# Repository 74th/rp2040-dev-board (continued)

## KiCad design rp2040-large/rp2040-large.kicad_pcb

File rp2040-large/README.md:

# RP2040 large board

RP2040 を手ではんだづけするのにトライしてみた開発ボードです。

Raspberry Pi PICO と同じピンレイアウトで、Flash を好きなサイズのものに置き換えて使うことができます。

RP2040 の実装の際には、細く切ったマスキングテープを使って位置合わせをしてから、実装すると成功率が上がります。

## v1.5.2

- 回路図 [PDF](./rp2040-large-semantics-1.5.2.pdf) [kicanvas](https://kicanvas.org/?github=https%3A%2F%2Fgithub.com%2F74th%2Frp2040-dev-board%2Fblob%2Frp2040-large%2F1.5.2%2Frp2040-large%2Frp2040-large.kicad_sch)
- PCB [kicanvas](https://kicanvas.org/?github=https%3A%2F%2Fgithub.com%2F74th%2Frp2040-dev-board%2Fblob%2Frp2040-large%2F1.5.2%2Frp2040-large%2Frp2040-large.kicad_pcb)

### features

- USB 電源保護 IC として [CH213K](https://www.wch-ic.com/products/CH213.html) を追加

### BOM

| Reference           | Name                                  | Quantity |
| ------------------- | ------------------------------------- | -------- |
| C1, C4              | Capacitor 0805 10uF                   | 2        |
| C2, C3              | Capacitor 0805 10-33pF                | 2        |
| C5, C7, C10         | Capacitor 0805 1uF                    | 3        |
| C6, C8, C9, C11-C16 | Capacitor 0805 100nF                  | 9        |
| D1                  | LED 0805 RED                          | 1        |
| D2                  | LED 0805 BLUE                         | 1        |
| J1                  | USB Type-C Receptacle                 | 1        |
| R1, R11             | Resistor 0805 1kΩ                     | 2        |
| R2, R3, R7          | Resistor 0805 5.1kΩ                   | 3        |
| R4, R5              | Resistor 0805 27Ω                     | 2        |
| R6, R10             | Resistor 0805 10kΩ                    | 2        |
| R8                  | Resistor 0805 1RΩ                     | 1        |
| R9                  | Resistor 0805 200Ω                    | 1        |
| SW1, SW2            | Button SKRPABE010                     | 2        |
| U1                  | USB Power Protection IC SOT-23 CH213K | 1        |
| U2                  | Regulator 3.3V SOT-89 AMS1117-3.3     | 1        |
| U3                  | Flash SOIC-8 W25Q32JVS                | 1        |
| U4                  | MCU Raspberry Pi RP2040               | 1        |
| Y1                  | Crystal 3225 12MHz                    | 1        |

### BOM

## v1.4.0

- 回路図 [PDF](./rp2040-large-semantics-1.4.0.pdf) [kicanvas](https://kicanvas.org/?github=https%3A%2F%2Fgithub.com%2F74th%2Frp2040-dev-board%2Fblob%2Frp2040-large%2Fv1.4.0%2Frp2040-large%2Frp2040-large.kicad_sch)
- PCB [kicanvas](https://kicanvas.org/?github=https%3A%2F%2Fgithub.com%2F74th%2Frp2040-dev-board%2Fblob%2Frp2040-large%2Fv1.4.0%2Frp2040-large%2Frp2040-large.kicad_pcb)

| ID                         | package                             | Value   | Num |
| -------------------------- | ----------------------------------- | ------- | --- |
| C1,C2,C4,C6-C8,C10,C13,C16 | 0805in 2012mm SMD Capacitor         | 100nF   | 9   |
| C3,C5,C9                   | 0805in 2012mm SMD Capacitor         | 1uF     | 3   |
| C11,C12                    | 0603in 1608mm SMD Capacitor         | 27pF    | 2   |
| C14,C15                    | 0805in 2012mm SMD Capacitor         | 10uF    | 2   |
| R1,R2                      | 0805in 2012mm SMD Resistor          | 27.4R   | 2   |
| R3,R6                      | 0805in 2012mm SMD Resistor          | 1kR     | 2   |
| R7                         | 0805in 2012mm SMD Resistor          | 1kR(NC) | 1   |
| R4,R5                      | 0805in 2012mm SMD Resistor          | 5.1kR   | 2   |
| R8                         | 0805in 2012mm SMD Resistor          | 10kR    | 1   |
| R9                         | 0805in 2012mm SMD Resistor          | 200R    | 1   |
| R10                        | 0805in 2012mm SMD Resistor          | 1R      | 1   |
| U1                         | RP2040                              |         | 1   |
| U2                         | W25Q32BVSSIG                        |         | 1   |
| U3                         | AMS 1117-3.3V                       |         | 1   |
| P1                         | USB 2.0 Type-C MidMount Socket      |         | 1   |
| Y1                         | 3325mm SMD Quartz Resonator Crystal | 12MHz   | 1   |
| SW1,SW2                    | 3x4x2.5mm SMD Tactile Switch        |         | 2   |

## v1.3.1

| ID                         | package                             | Value | Num |
| -------------------------- | ----------------------------------- | ----- | --- |
| C1,C2,C4,C6-C8,C10,C13,C16 | 0805in 2012mm SMD Capacitor         | 100nF | 9   |
| C3,C5                      | 0805in 2012mm SMD Capacitor         | 1uF   | 2   |
| C11,C12                    | 0603in 1608mm SMD Capacitor         | 27pF  | 2   |
| C14,C15                    | 0805in 2012mm SMD Capacitor         | 10uF  | 2   |
| R1,R2                      | 0805in 2012mm SMD Resistor          | 27.4R | 2   |
| R3,R6,R7                   | 0805in 2012mm SMD Resistor          | 1kR   | 2   |
| R4,R5                      | 0805in 2012mm SMD Resistor          | 5.1kR | 2   |
| R8                         | 0805in 2012mm SMD Resistor          | 10kR  | 1   |
| U1                         | RP2040                              |       | 1   |
| U2                         | W25Q32BVSSIG                        |       | 1   |
| U3                         | AMS 1117-3.3V                       |       | 1   |
| P1                         | USB 2.0 Type-C MidMount Socket      |       | 1   |
| Y1                         | 3325mm SMD Quartz Resonator Crystal | 12MHz | 1   |

## 部品の購入先

[../parts/README.md](../parts/README.md)

## RP2040 手はんだ実装挑戦指南ガイド

74th の実装ノウハウをまとめたガイドを用意しています。初めて挑戦される方はぜひおよみください。

https://docs.google.com/document/d/1oHzV6qEClttqfrnbo-PlUElAemhTQe8-u3ijAKLZYF0/edit#heading=h.1b8zdysibsw9

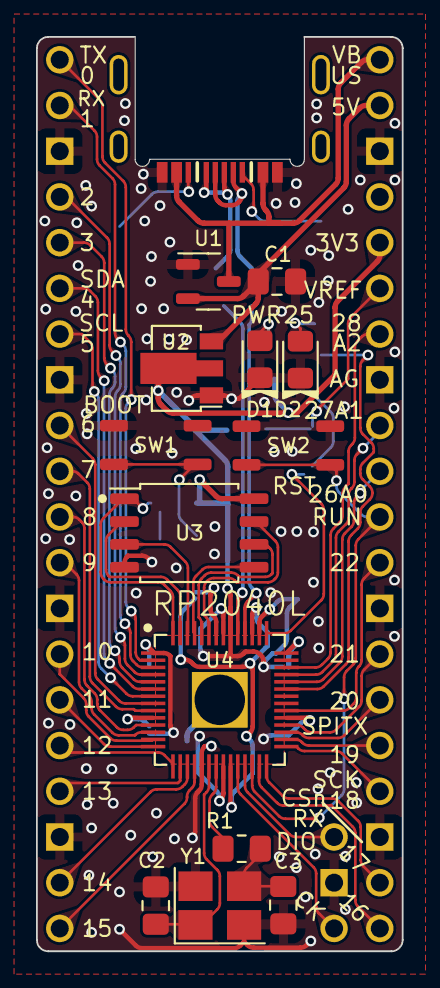
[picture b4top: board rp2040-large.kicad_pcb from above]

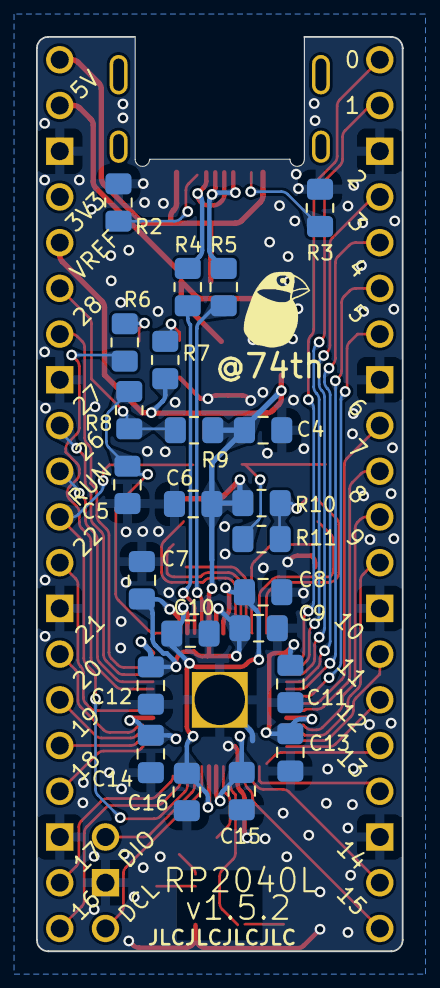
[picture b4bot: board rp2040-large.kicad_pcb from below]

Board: 2 copper layers, 20.3 x 50.8 mm, 41 parts (25 on the bottom side), 55 nets.

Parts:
C1, C4: 10uF; Capacitor_0805_2012
C2, C3: 27pF; Capacitor_0805_2012
C5, C7, C10: 1uF; Capacitor_0805_2012
C6, C8, C9, C11, C12, C13, C14, C15, C16: 100nF; Capacitor_0805_2012
CH1: RasperryPiPico PinOut; PinOut_RaspberryPiPico
CH2: SWD; PinOut_SWD_3Pin
D1: RED; LED_0805_2012
D2: BLUE; LED_0805_2012
J1: 217179-0001; Connector_USB-C-Receptacle_SMT_12-Pin_MidMount_Simple
MISC-ACCOUNTTEXT: Logo_74th_text
MISC-ICON: LOGO; Logo_74th_5mm
R1, R11: 1kR; Register_0805_2012
R2, R3: 5.1kR; Register_0805_2012
R4, R5: 27.4R; Register_0805_2012
R6: 10k; Register_0805_2012
R7: 5.1k; Register_0805_2012
R8: 1R; Register_0805_2012
R9: 200R; Register_0805_2012
R10: 10kR; Register_0805_2012
SW1, SW2: SW_Push; PushButton_SKRPABE010
U1: CH213K; Package_SOT-23
U2: AZ1117-3.3; Package_SOT-89-3
U3: W25Q32JVS; Package_SOIC-8_5.23x5.23mm_P1.27mm
U4: RP2040; Package_QFN-54-1EP_7x7mm_P0.4mm_EP3.1x3.1mm_hand
Y1: Crystal_GND24; Crystal_SMD_3225-4Pin_3.2x2.5mm_HandSoldering

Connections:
+1V1: C8.1, C10.1, C16.1, U4.23 (DVDD), U4.45 (VREG_VOUT), U4.50 (DVDD)
+3V3: C4.1, C6.1, C7.1, C9.1, C11.1, C12.1, C13.1, C14.1, C15.1, CH1.36 (3V3), R7.2, R9.2, R10.2, U2.2 (VO), U3.8 (VCC), U4.1 (IOVDD), U4.10 (IOVDD), U4.22 (IOVDD), U4.33 (IOVDD), U4.42 (IOVDD), U4.44 (VREG_IN), U4.48 (USB_VDD), U4.49 (IOVDD)
+5V: C1.1, CH1.39 (VSYS), U1.2 (VO-), U2.3 (VI)
/ADC_VREF: CH1.35 (VREF), R8.2, R9.1
/BOOTSEL: R11.1, SW1.2
/GPIO0: CH1.1 (0), U4.2 (GPIO0)
/GPIO1: CH1.2 (1), U4.3 (GPIO1)
/GPIO2: CH1.4 (2), U4.4 (GPIO2)
/GPIO3: CH1.5 (3), U4.5 (GPIO3)
/GPIO4: CH1.6 (4), U4.6 (GPIO4)
/GPIO5: CH1.7 (5), U4.7 (GPIO5)
/GPIO6: CH1.9 (6), U4.8 (GPIO6)
/GPIO7: CH1.10 (7), U4.9 (GPIO7)
/GPIO8: CH1.11 (8), U4.11 (GPIO8)
/GPIO9: CH1.12 (9), U4.12 (GPIO9)
/GPIO10: CH1.14 (10), U4.13 (GPIO10)
/GPIO11: CH1.15 (11), U4.14 (GPIO11)
/GPIO12: CH1.16 (12), U4.15 (GPIO12)
/GPIO13: CH1.17 (13), U4.16 (GPIO13)
/GPIO14: CH1.19 (14), U4.17 (GPIO14)
/GPIO15: CH1.20 (15), U4.18 (GPIO15)
/GPIO16: CH1.21 (16), U4.27 (GPIO16)
/GPIO17: CH1.22 (17), U4.28 (GPIO17)
/GPIO18: CH1.24 (18), U4.29 (GPIO18)
/GPIO19: CH1.25 (19), U4.30 (GPIO19)
/GPIO20: CH1.26 (20), U4.31 (GPIO20)
/GPIO21: CH1.27 (21), U4.32 (GPIO21)
/GPIO22: CH1.29 (22), U4.34 (GPIO22)
/GPIO26: CH1.31 (26), U4.38 (GPIO26_ADC0)
/GPIO27: CH1.32 (27), U4.39 (GPIO27_ADC1)
/GPIO28: CH1.34 (28), U4.40 (GPIO28_ADC2)
/LED: D2.2 (A), R6.2
/QSPI_CLK: U3.6 (CLK), U4.52 (QSPI_SCLK)
/QSPI_SD0: U3.5 (DI(IO0)), U4.53 (QSPI_SD0)
/QSPI_SD1: U3.2 (DO(IO1)), U4.55 (QSPI_SD1)
/QSPI_SD2: U3.3 (IO2), U4.54 (QSPI_SD2)
/QSPI_SD3: U3.7 (IO3), U4.51 (QSPI_SD3)
/QSPI_SS: R10.1, R11.2, U3.1 (~CS), U4.56 (QSPI_SS)
/RUN: CH1.30 (RUN), SW2.2, U4.26 (RUN)
/SWCLK: CH2.1 (SWCLK), U4.24 (SWCLK)
/SWDIO: CH2.3 (SWDIO), U4.25 (SWD)
/USB_DM: R4.2, U4.46 (USB_DM)
/USB_DP: R5.2, U4.47 (USB_DP)
/XIN: C2.2, U4.20 (XIN), Y1.1
/XOUT: R1.1, U4.21 (XOUT)
GND: C1.2, C2.1, C3.1, C4.2, C5.2, C6.2, C7.2, C8.2, C9.2, C10.2, C11.2, C12.2, C13.2, C14.2, C15.2, C16.2, CH1.3 (GND), CH1.8 (GND), CH1.13 (GND), CH1.18 (GND), CH1.23 (GND), CH1.28 (GND), CH1.33 (GND), CH1.38 (GND), CH2.2 (GND), D1.1 (K), D2.1 (K), J1.4 (GND), R2.2, R3.2, SW1.1, SW2.1, U1.1 (GND), U2.1 (GND), U3.4 (GND), U4.19 (TESTEN), U4.57 (GND), Y1.2, Y1.4
unnamed: C3.2, R1.2, Y1.3
unnamed: D1.2 (A), R7.1
unnamed: J1.5 (CC1), R2.1
unnamed: J1.6 (CC2), R3.1
unnamed: J1.3 (D+), R5.1
unnamed: J1.2 (D-), R4.1
unnamed: C5.1, R8.1, U4.43 (ADC_AVDD)
unnamed: R6.1, U4.37 (GPIO25)
VBUS: CH1.40 (VBUS), J1.1 (VBUS), U1.3 (VI+)

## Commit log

2022-06-11 rp2040-large
2022-06-18 rp2040-promicro
2022-07-11 pro micro board
2022-07-11 update BOM
2022-08-27 rp2040-large v1.4.0
2022-12-04 io tester
2022-12-04 update parts list
2022-12-31 promicro v2
2023-01-01 update datasheet
2023-01-01 rp-promicro v2.0.0
2023-01-15 古い記述を削除
2023-01-15 fix for GPIO29
2023-01-22 delete
2023-01-22 update photo
2023-02-08 rp2040-promicro/2.0.1
2023-07-22 add kicanvas
2023-07-22 fix photo size
2023-09-17 v2.0.1で最後に位置を整列したのが未コミットだった
2023-09-17 fix BOM
2023-09-18 fix v2.0.1
2023-11-19 rp2040-large/1.5.0
2023-12-02 rp2040-large/1.5.1
2023-12-22 1.5.2
2024-01-25 update AKIZUKI URL
2024-03-15 rp2040-supporter
2024-03-15 add LICENSE
2024-07-28 rp2040-promicro/2.0.2
2024-08-10 wired
2024-08-10 rename
2024-08-19 rp2350-testing/1.0.0
2024-09-13 rp2350a-full
2024-09-13 remove io-tester
2024-09-15 add pin map
2024-09-15 pinmap
2024-09-15 pin map
2024-09-15 remove unused files
2024-09-15 update partslist
2025-01-12 fix typo
